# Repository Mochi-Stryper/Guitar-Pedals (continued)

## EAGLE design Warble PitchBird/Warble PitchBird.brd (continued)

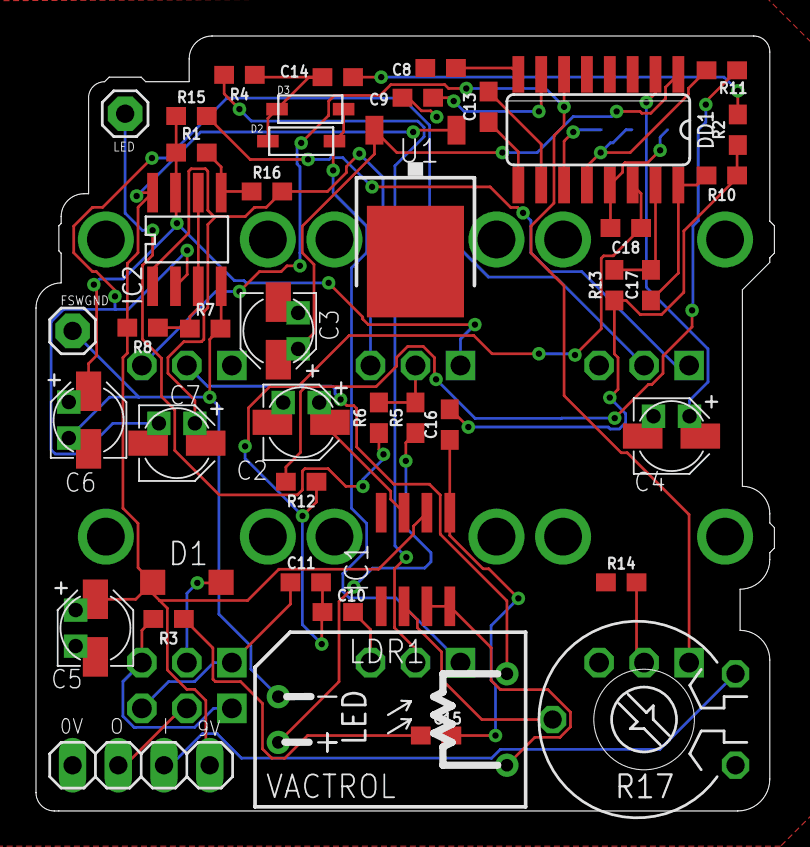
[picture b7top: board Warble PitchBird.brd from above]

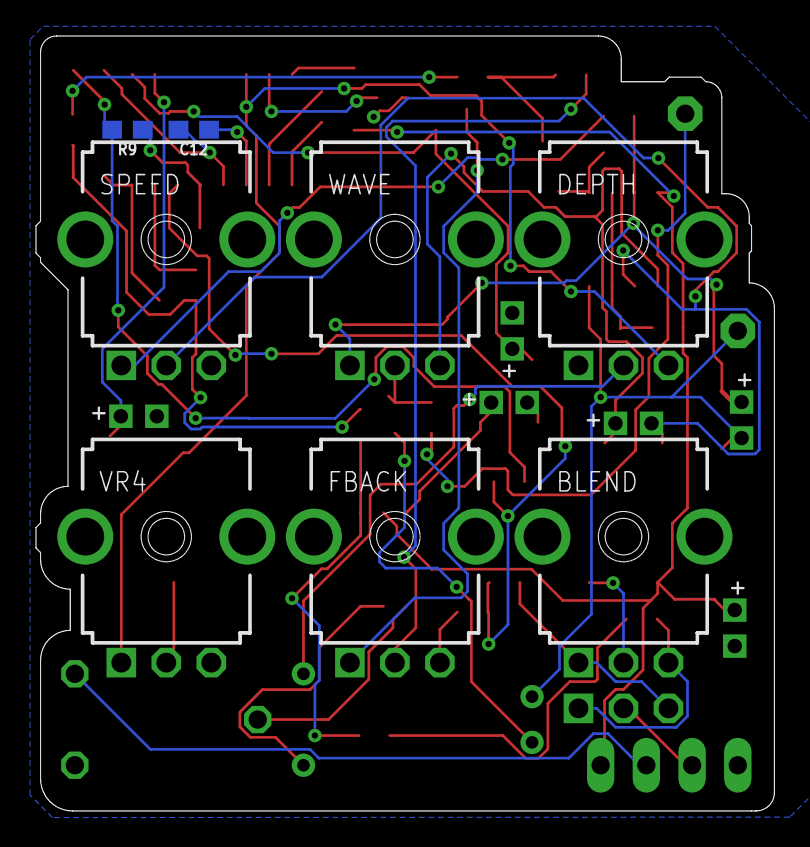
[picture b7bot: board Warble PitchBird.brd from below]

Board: 2 copper layers, 41.0 x 43.1 mm, 51 parts (8 on the bottom side), 42 nets.

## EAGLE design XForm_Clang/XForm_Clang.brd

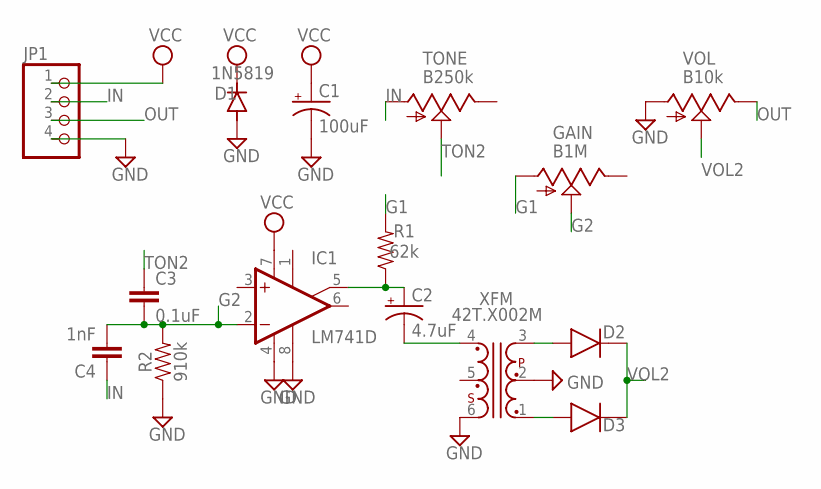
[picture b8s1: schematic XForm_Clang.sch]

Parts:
C1: 100uF; PAN_B_SMD+THRU
C2: 4.7uF; PAN_B_SMD+THRU
C3: 0.1uF; 0603
C4: 1nF; 0603
D1: 1N5819; SOD123
D2, D3: 1N4148; D35-10
GAIN: B1M; 9MM_SNAP-IN_POT
IC1: LM741D; SO08
JP1: PINHD-1X4; 1X04
R1: 62k; 0603
R2: 910k; 0603
TONE: B250k; 9MM_SNAP-IN_POT
VOL: B10k; 9MM_SNAP-IN_POT
XFM: 42T.X002M; 42TM

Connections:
G1: GAIN.1 (A), R1.2
G2: C3.2, C4.2, GAIN.2 (S), IC1.2 (-IN), R2.2
GND: C1.-, C1.-- (-), D1.A, IC1.4 (V-), IC1.8 (OPT), JP1.4, R2.1, VOL.1 (A), XFM.2, XFM.6
IN: C4.1, JP1.2, TONE.1 (A)
unnamed: D2.A, XFM.3
unnamed: C2.+, C2.++ (+), IC1.5 (ON2), R1.1
unnamed: C2.-, C2.-- (-), XFM.4
unnamed: D3.A, XFM.1
OUT: JP1.3, VOL.3 (E)
TON2: C3.1, TONE.2 (S)
VCC: C1.+, C1.++ (+), D1.C, IC1.7 (V+), JP1.1
VOL2: D2.K, D3.K, VOL.2 (S)

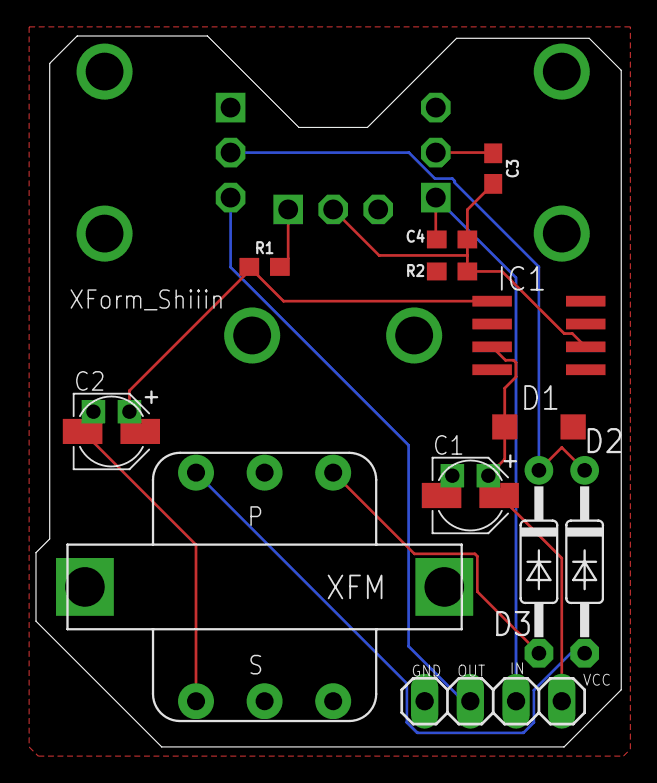
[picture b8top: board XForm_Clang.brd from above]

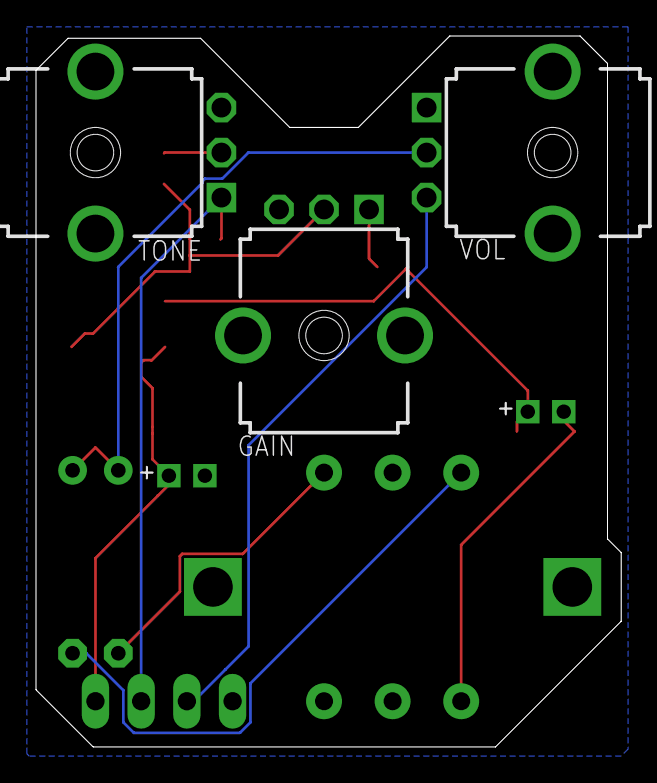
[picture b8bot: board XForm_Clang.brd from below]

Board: 2 copper layers, 32.5 x 39.5 mm, 15 parts (3 on the bottom side), 12 nets.
